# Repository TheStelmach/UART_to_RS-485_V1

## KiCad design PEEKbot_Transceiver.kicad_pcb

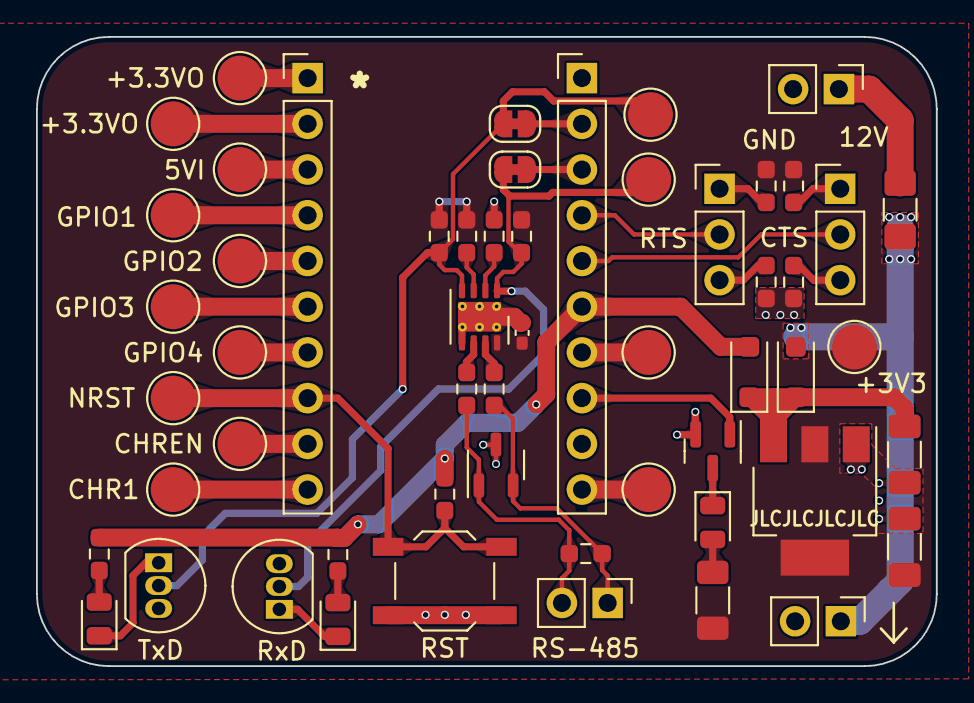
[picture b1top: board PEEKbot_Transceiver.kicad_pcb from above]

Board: 2 copper layers, 50.0 x 35.0 mm, 55 parts (0 on the bottom side), 41 nets.

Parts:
5VI: TestPoint_Probe; TestPoint_Pad_D2.5mm
+3.3VO, +3.3VO#2, +3V3: TestPoint_Probe; TestPoint_Pad_D2.5mm
C1, C2: 10uF; C_1206_3216Metric_Pad1.33x1.80mm_HandSolder
C3: 100nF; C_0402_1005Metric_Pad0.74x0.62mm_HandSolder
CHR0, CHR1: TestPoint_Probe; TestPoint_Pad_D2.5mm
CHREN: TestPoint_Probe; TestPoint_Pad_D2.5mm
D1, D3: 1N4007; D_SOD-123F
D2, D4, D5: LED; LED_0805_2012Metric
ESD1: SM712_SOT23; SOT-23-3
F1: Polyfuse_Small; Fuse_1206_3216Metric_Pad1.42x1.75mm_HandSolder
GPIO1, GPIO2, GPIO3, GPIO4: TestPoint_Probe; TestPoint_Pad_D2.5mm
J1, J4, J7: Conn_01x02; PinHeader_1x02_P2.54mm_Vertical
J2, J3: Conn_01x10_Pin; PinHeader_1x10_P2.54mm_Vertical
J5, J6: Conn_01x03_Pin; PinHeader_1x03_P2.54mm_Vertical
JP1, JP2: SolderJumper_2_Open; SolderJumper-2_P1.3mm_Bridged_RoundedPad1.0x1.5mm
NRST: TestPoint_Probe; TestPoint_Pad_D2.5mm
Q1, Q2: 2N3906; TO-92_Inline
Q3: 2N7002K; SOT-23
R1, R2, R5: 1k; R_0603_1608Metric_Pad0.98x0.95mm_HandSolder
R3, R4, R7, R8, R9, R10, R11, R12: 10k; R_0603_1608Metric_Pad0.98x0.95mm_HandSolder
R6: 220; R_1206_3216Metric_Pad1.30x1.75mm_HandSolder
R13, R14: 10; R_0603_1608Metric_Pad0.98x0.95mm_HandSolder
R15: 50; R_0603_1608Metric_Pad0.98x0.95mm_HandSolder
SW1: SW_SPST; SW_SPST_TL3342
TP1, TP2: TestPoint_Probe; TestPoint_Pad_D2.5mm
U1: AP1117-33; SOT-223-3_TabPin2
U2: SN65HVD72DRBR; VSON-8-1EP_3x3mm_P0.65mm_EP1.65x2.4mm_ThermalVias
USB_SUSPENDb: TestPoint_Probe; TestPoint_Pad_D2.5mm

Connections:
+3V3: +3V3.1, C2.1, C3.1, R3.1, R6.1, R7.1, R10.1, R11.1, R12.1, U1.2 (VO), U2.8 (VCC)
+12V: D1.2 (A), F1.2, J4.1
/CTS: J3.5, J6.2
/NRST: J2.8, NRST.1, R5.2, SW1.1 (A)
/OUT+: ESD1.1 (A1), J7.2, R13.1, R15.1
/OUT-: ESD1.2 (A2), J7.1, R14.1, R15.2
/RTS: J3.4, J5.2
/RxD: JP2.2 (B), Q2.2 (B), R12.2, TP2.1, U2.1 (R)
/TxD: JP1.2 (B), Q1.2 (B), R11.2, TP1.1, U2.4 (D)
/USB_SUSPEND: J3.8, Q3.1 (G)
GND: C1.2, C2.2, C3.2, ESD1.3 (common), J1.2, J3.1, J3.9, J4.2, Q1.3 (C), Q2.3 (C), Q3.2 (S), R4.2, R8.2, R9.2, SW1.2 (B), U1.1 (GND), U2.5 (GND), U2.9 (EPAD)
unnamed: C1.1, D1.1 (K), D3.1 (K), U1.3 (VI)
unnamed: D2.2 (A), R1.2
unnamed: D2.1 (K), Q1.1 (E)
unnamed: D4.2 (A), R2.2
unnamed: D4.1 (K), Q2.1 (E)
unnamed: D5.2 (A), R6.2
unnamed: D5.1 (K), Q3.3 (D)
unnamed: F1.1, J1.1
unnamed: +3.3VO#2.1, J2.1
unnamed: +3.3VO.1, J2.2
unnamed: 5VI.1, J2.3
unnamed: GPIO1.1, J2.4
unnamed: GPIO2.1, J2.5
unnamed: GPIO3.1, J2.6
unnamed: GPIO4.1, J2.7
unnamed: CHREN.1, J2.9
unnamed: CHR1.1, J2.10
unnamed: J3.2, JP1.1 (A)
unnamed: J3.3, JP2.1 (A)
unnamed: J3.7, USB_SUSPENDb.1
unnamed: CHR0.1, J3.10
unnamed: J5.1, R3.2
unnamed: J5.3, R4.1
unnamed: J6.1, R7.2
unnamed: J6.3, R8.1
unnamed: R9.1, U2.2 (*RE)
unnamed: R13.2, U2.6 (A)
unnamed: R14.2, U2.7 (B)
unnamed: R10.2, U2.3 (DE)
VBUS: D3.2 (A), J3.6, R1.1, R2.1, R5.1

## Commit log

2024-03-30 UART to RS-485 transceiver KiCAD schematics added
